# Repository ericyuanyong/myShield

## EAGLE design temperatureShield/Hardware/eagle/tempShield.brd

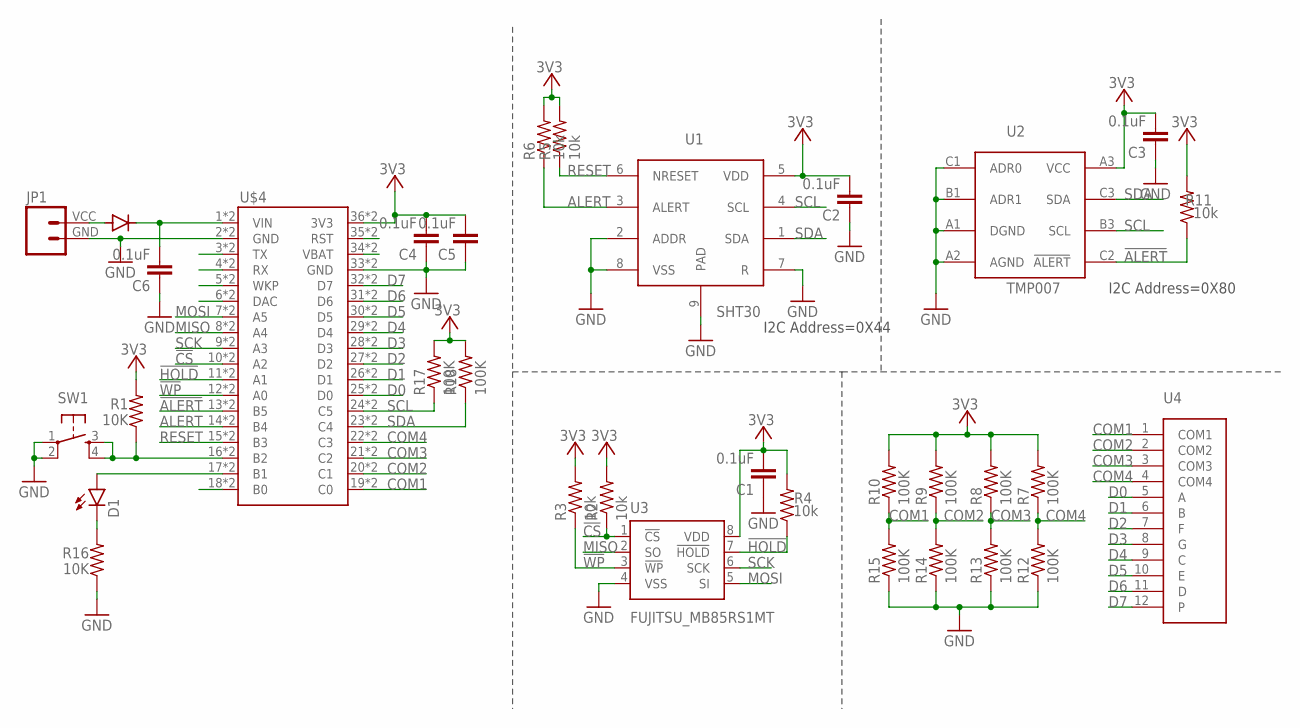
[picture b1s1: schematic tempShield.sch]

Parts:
C1, C2, C3, C4, C5, C6: 0.1uF; 0603-CAP
D1: LED0603; LED-0603
JP1: SPARKFUN-CONNECTORS_M024UCON-15767; SPARKFUN-CONNECTORS_JST-2-SMD-VERT
R1, R16: 10K; R0402
R2, R3, R4, R5, R6, R11: 10k; 0603-RES
R7, R8, R9, R10, R12, R13, R14, R15, R17, R18: 100K; R0402
SW1: SWITCH_SPST_4_PIN; TACTILE-SWITCH-SMD
U1: SHT30
U2: TMP007; TMP007_1
U3: FUJITSU_MB85RS1MT; FUJITSU_SO08
U4: LCD
U$1: PARTICLE_DIODE_NT; PARTICLE_DIODE-DO-220AA_NT(SMP)
U$4: MICROBUILDER_ELECTRON_SMT

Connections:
!ALERT: R11.1, U2.C2 (!ALERT!), U$4.13 (B5), U$4.13B (B5)
!CS: R2.1, U3.1 (!CS), U$4.10 (A2), U$4.10B (A2)
!HOLD: R4.1, U3.7 (!HOLD), U$4.11 (A1), U$4.11B (A1)
!WP: R3.1, U3.3 (!WP), U$4.12 (A0), U$4.12B (A0)
+3V3: C1.2, C2.2, C3.2, C4.2, C5.2, R1.2, R2.2, R3.2, R4.2, R5.2, R6.2, R7.2, R8.2, R9.2, R10.2, R11.2, R17.2, R18.2, U1.5 (VDD), U2.A3 (VCC), U3.8 (VDD), U$4.36 (3V3), U$4.36B (3V3)
ALERT: R6.1, U1.3 (ALERT), U$4.14 (B4), U$4.14B (B4)
COM1: R10.1, R15.2, U4.1 (COM1), U$4.19 (C0), U$4.19B (C0)
COM2: R9.1, R14.2, U4.2 (COM2), U$4.20 (C1), U$4.20B (C1)
COM3: R8.1, R13.2, U4.3 (COM3), U$4.21 (C2), U$4.21B (C2)
COM4: R7.1, R12.2, U4.4 (COM4), U$4.22 (C3), U$4.22B (C3)
D0: U4.5 (A), U$4.25 (D0), U$4.25B (D0)
D1: U4.6 (B), U$4.26 (D1), U$4.26B (D1)
D2: U4.7 (F), U$4.27 (D2), U$4.27B (D2)
D3: U4.8 (G), U$4.28 (D3), U$4.28B (D3)
D4: U4.9 (C), U$4.29 (D4), U$4.29B (D4)
D5: U4.10 (E), U$4.30 (D5), U$4.30B (D5)
D6: U4.11 (D), U$4.31 (D6), U$4.31B (D6)
D7: U4.12, U$4.32 (D7), U$4.32B (D7)
GND: C1.1, C2.1, C3.1, C4.1, C5.1, C6.1, JP1.GND (1), R12.1, R13.1, R14.1, R15.1, R16.1, SW1.1, SW1.2, U1.2 (ADDR), U1.7 (R), U1.8 (VSS), U1.9 (PAD), U2.A1 (DGND), U2.A2 (AGND), U2.B1 (ADR1), U2.C1 (ADR0), U3.4 (VSS), U$4.2 (GND), U$4.2B (GND), U$4.33 (GND), U$4.33B (GND)
MISO: U3.2 (SO), U$4.8 (A4), U$4.8B (A4)
MOSI: U3.5 (SI), U$4.7 (A5), U$4.7B (A5)
unnamed: C6.2, U$1.CATHODE, U$4.1 (VIN), U$4.1B (VIN)
unnamed: D1.A, U$4.17 (B1), U$4.17B (B1)
unnamed: JP1.VCC (2), U$1.ANODE
unnamed: R1.1, SW1.3, SW1.4, U$4.16 (B2), U$4.16B (B2)
unnamed: D1.C, R16.2
unnamed: U$4.35 (RST), U$4.35B (RST)
unnamed: U$4.34 (VBAT), U$4.34B (VBAT)
unnamed: U$4.3 (TX), U$4.3B (TX)
unnamed: U$4.4 (RX), U$4.4B (RX)
unnamed: U$4.5 (WKP), U$4.5B (WKP)
unnamed: U$4.6 (DAC), U$4.6B (DAC)
unnamed: U$4.18 (B0), U$4.18B (B0)
RESET: R5.1, U1.6 (NRESET), U$4.15 (B3), U$4.15B (B3)
SCK: U3.6 (SCK), U$4.9 (A3), U$4.9B (A3)
SCL: R17.1, U1.4 (SCL), U2.B3 (SCL), U$4.24 (C5), U$4.24B (C5)
SDA: R18.1, U1.1 (SDA), U2.C3 (SDA), U$4.23 (C4), U$4.23B (C4)

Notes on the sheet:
I2C Address=0X44
I2C Address=0X80

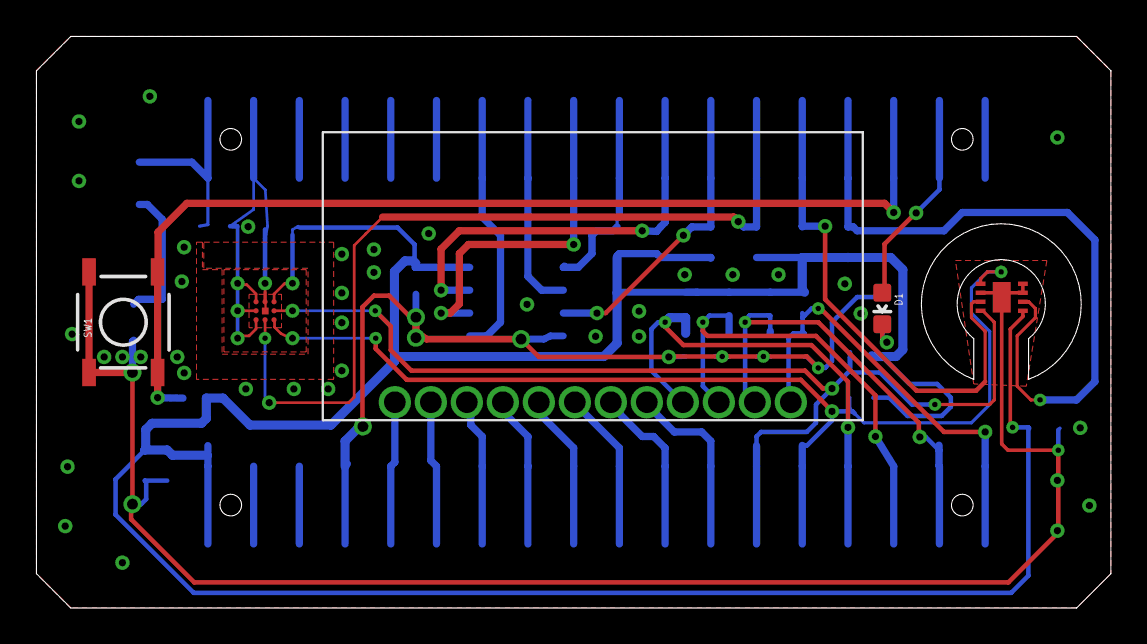
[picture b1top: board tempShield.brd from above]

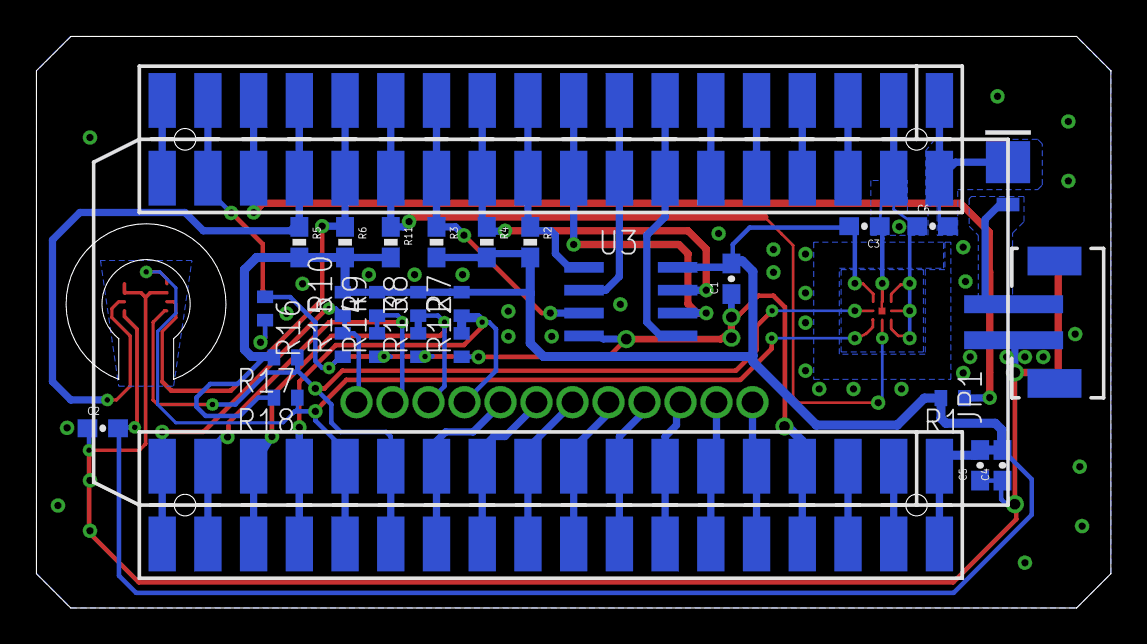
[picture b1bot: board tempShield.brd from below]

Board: 2 copper layers, 59.7 x 31.8 mm, 33 parts (28 on the bottom side), 37 nets.

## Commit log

2016-12-15 create a folder for temperature sensor
2016-12-18 still work on the schematic
2016-12-20 finished the schematic and part of the layout
2016-12-22 Keep on the layout
2016-12-23 update a little bit
2016-12-23 UPATE A LITTLE BIT AGAIN
2016-12-23 udpate little
2016-12-23 almost finish the layout,the package of diode need to be double check
2016-12-24 change the pad for BGA chip and generate the gerber
2016-12-25 add copper for power trace
2017-06-16 add the test code for asset tracker

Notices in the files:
parts and their libraries:
SparkFun-Resistors: Licensing: Creative Commons ShareAlike 4.0 International - https://creativecommons.org/licenses/by-sa/4.0
